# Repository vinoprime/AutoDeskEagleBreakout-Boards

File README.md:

# AutoDeskEagleBreakout-Boards
BraekoutBoards

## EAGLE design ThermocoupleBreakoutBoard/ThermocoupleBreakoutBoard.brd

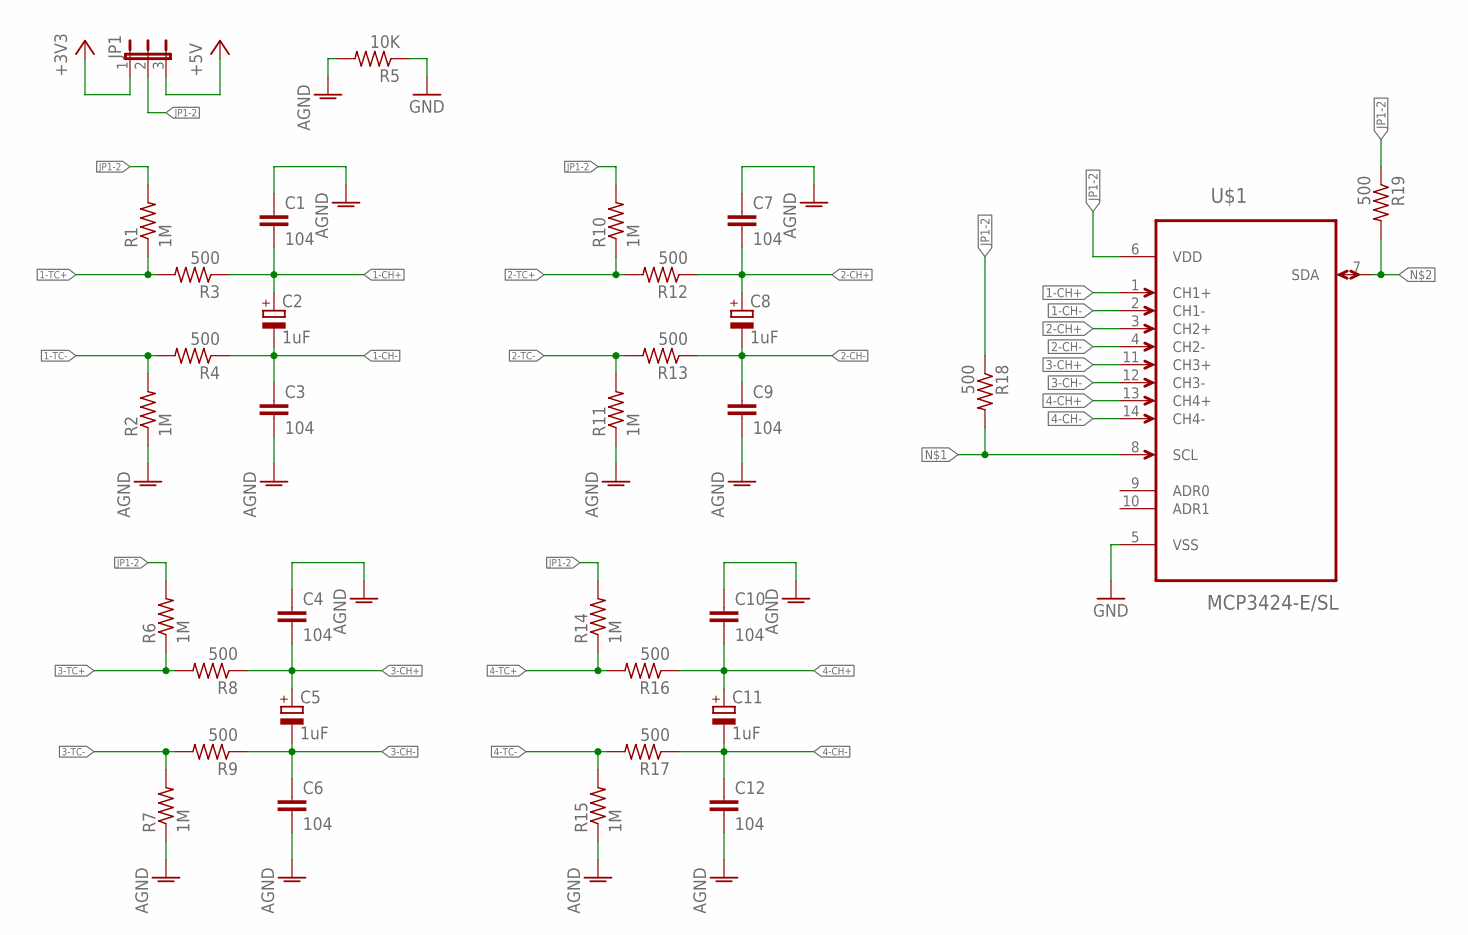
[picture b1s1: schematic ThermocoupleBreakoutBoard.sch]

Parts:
C1, C3, C4, C6, C7, C9, C10, C12: 104; C1206
C2, C5, C8, C11: 1uF; E2,5-6
JP1: JP2E; JP2
R1, R2, R6, R7, R10, R11, R14, R15: 1M; M1206
R3, R4, R8, R9, R12, R13, R16, R17, R18, R19: 500; M1206
R5: 10K; M1206
U$1: MCP3424-E/SL; SOIC127P600X175-14N

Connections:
1-CH+: C1.2, C2.+, R3.1, U$1.1 (CH1+)
1-CH-: C2.-, C3.1, R4.1, U$1.2 (CH1-)
1-TC+: R1.1, R3.2
1-TC-: R2.2, R4.2
2-CH+: C7.2, C8.+, R12.1, U$1.3 (CH2+)
2-CH-: C8.-, C9.1, R13.1, U$1.4 (CH2-)
2-TC+: R10.1, R12.2
2-TC-: R11.2, R13.2
3-CH+: C4.2, C5.+, R8.1, U$1.11 (CH3+)
3-CH-: C5.-, C6.1, R9.1, U$1.12 (CH3-)
3-TC+: R6.1, R8.2
3-TC-: R7.2, R9.2
4-CH+: C10.2, C11.+, R16.1, U$1.13 (CH4+)
4-CH-: C11.-, C12.1, R17.1, U$1.14 (CH4-)
4-TC+: R14.1, R16.2
4-TC-: R15.2, R17.2
+3V3: JP1.1
+5V: JP1.3
AGND: C1.1, C3.2, C4.1, C6.2, C7.1, C9.2, C10.1, C12.2, R2.1, R5.2, R7.1, R11.1, R15.1
GND: R5.1, U$1.5 (VSS)
JP1-2: JP1.2, R1.2, R6.2, R10.2, R14.2, R18.1, R19.1, U$1.6 (VDD)
unnamed: R18.2, U$1.8 (SCL)
unnamed: R19.2, U$1.7 (SDA)

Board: 2 copper layers, 33 parts (0 on the bottom side), 21 nets, no tracks yet.

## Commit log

2017-11-15 ThermocoupleBreakoutBoard design started
2017-12-19 Duplicated 4-thermocouple input section
2017-12-19 Frame added in .sch
2017-12-20 Added MCP3424 Device and made routing
